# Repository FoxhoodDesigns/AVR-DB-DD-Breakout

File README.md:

# AVR DB/DD Breakout

This little Board is designed to allow for easy experimentation with AVR128DB32 and AVR64DD32 Microcontrollers.
It is very minimalist with only the AVR itself, A pair of standard LDO linear regulators (1117-5V and a 2112-3.3V), A simple power indicator and some jumpers for configuring the board and/or VDDIO2 to 3.3V or 5V.
Note: This relies on the Internal Oscillator which on the new generation of AVR chips can achieve pretty high speeds.

Both the DB and DD work. The DD is more suitable as a general purpose and is fairly cheap (comparable to a ATMega32PB), while the DB is more for bigger stuff. As one might guess by having up to a whopping 128Kb of Flash for code.

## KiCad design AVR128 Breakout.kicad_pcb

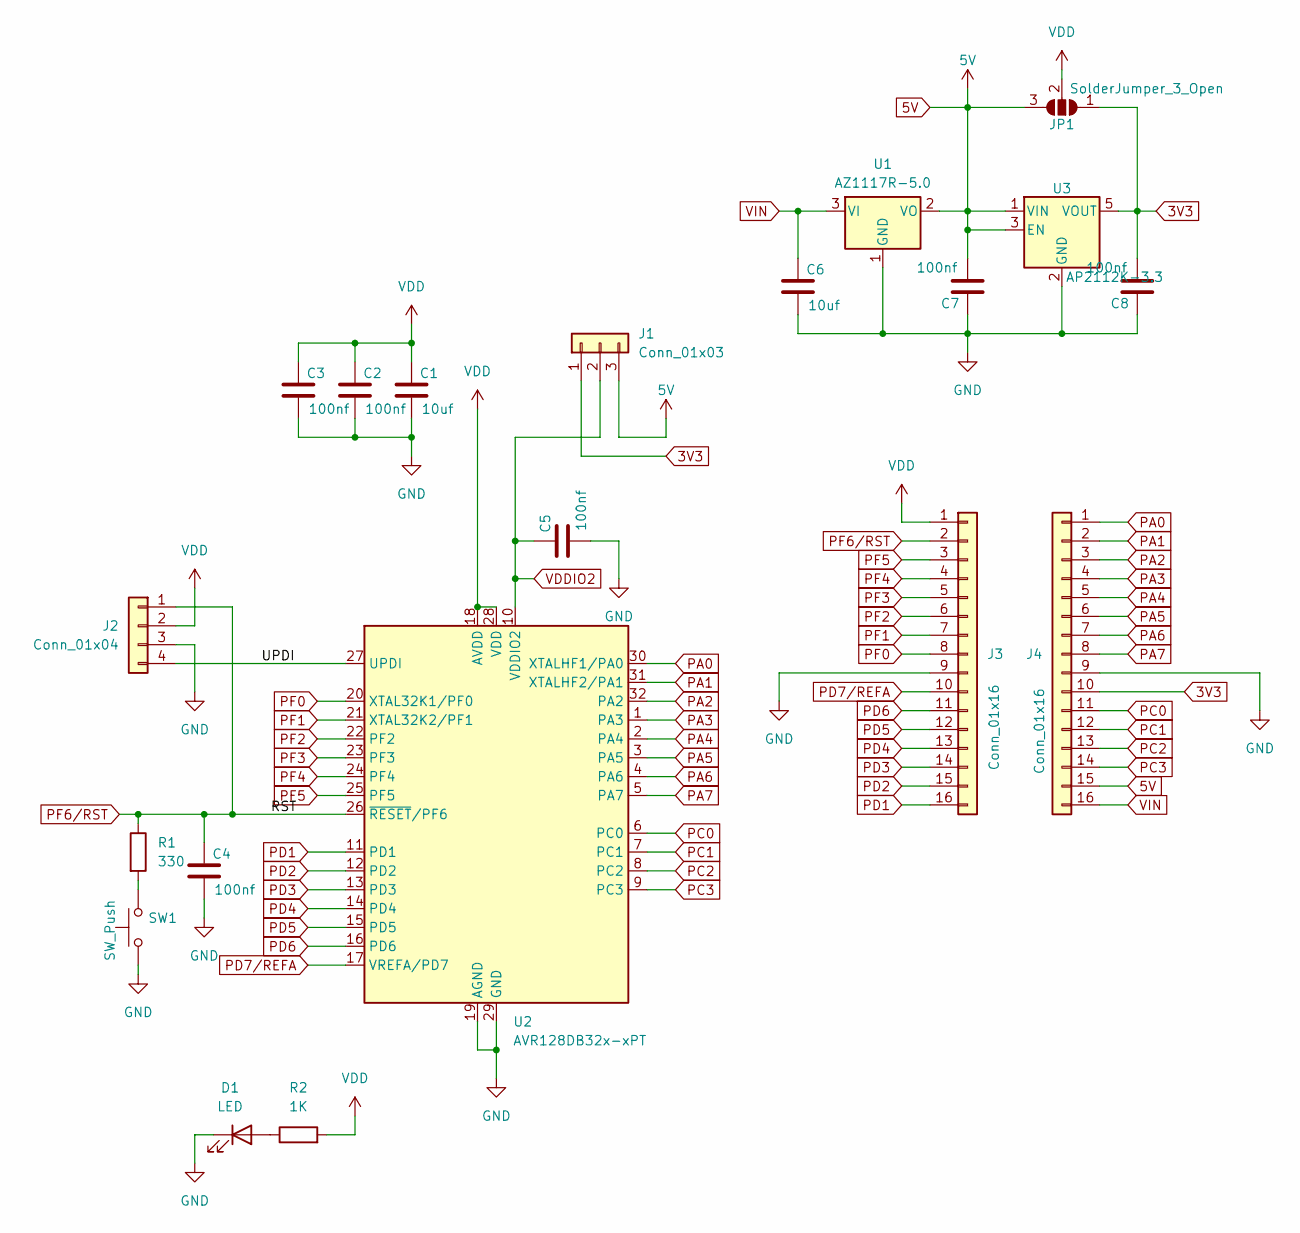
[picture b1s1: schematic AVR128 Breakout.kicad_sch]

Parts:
C1, C6: 10uf; C_1210_3225Metric_Pad1.33x2.70mm_HandSolder
C2, C3, C4, C5, C7, C8: 100nf; C_0805_2012Metric_Pad1.18x1.45mm_HandSolder
D1: LED; LED_0805_2012Metric_Pad1.15x1.40mm_HandSolder
J1: Conn_01x03; PinHeader_1x03_P2.54mm_Vertical
J2: Conn_01x04; PinHeader_1x04_P2.54mm_Vertical
J3, J4: Conn_01x16; PinHeader_1x16_P2.54mm_Vertical
JP1: SolderJumper_3_Open; SolderJumper-3_P1.3mm_Open_Pad1.0x1.5mm_NumberLabels
R1: 330; R_0805_2012Metric_Pad1.20x1.40mm_HandSolder
R2: 1K; R_0805_2012Metric_Pad1.20x1.40mm_HandSolder
SW1: SW_Push; SW_Push_1P1T_NO_Vertical_Wuerth_434133025816
U1: AZ1117R-5.0; SOT-89-3_Handsoldering
U2: AVR128DB32x-xPT; TQFP-32_7x7mm_P0.8mm
U3: AP2112K-3.3; SOT-23-5

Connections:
3V3: C8.2, J1.1, J4.10, JP1.1 (A), U3.5 (VOUT)
5V: C7.2, J1.3, J4.15, JP1.3 (B), U1.2 (VO), U3.1 (VIN), U3.3 (EN)
/UPDI: J2.4, U2.27 (UPDI)
GND: C1.2, C2.2, C3.2, C4.2, C5.2, C6.2, C7.1, C8.1, D1.1 (K), J2.3, J3.9, J4.9, SW1.1, U1.1 (GND), U2.19 (AGND), U2.29 (GND), U3.2 (GND)
unnamed: D1.2 (A), R2.1
unnamed: R1.2, SW1.2
PA0: J4.1, U2.30 (XTALHF1/PA0)
PA1: J4.2, U2.31 (XTALHF2/PA1)
PA2: J4.3, U2.32 (PA2)
PA3: J4.4, U2.1 (PA3)
PA4: J4.5, U2.2 (PA4)
PA5: J4.6, U2.3 (PA5)
PA6: J4.7, U2.4 (PA6)
PA7: J4.8, U2.5 (PA7)
PC0: J4.11, U2.6 (PC0)
PC1: J4.12, U2.7 (PC1)
PC2: J4.13, U2.8 (PC2)
PC3: J4.14, U2.9 (PC3)
PD1: J3.16, U2.11 (PD1)
PD2: J3.15, U2.12 (PD2)
PD3: J3.14, U2.13 (PD3)
PD4: J3.13, U2.14 (PD4)
PD5: J3.12, U2.15 (PD5)
PD6: J3.11, U2.16 (PD6)
PD7/REFA: J3.10, U2.17 (VREFA/PD7)
PF0: J3.8, U2.20 (XTAL32K1/PF0)
PF1: J3.7, U2.21 (XTAL32K2/PF1)
PF2: J3.6, U2.22 (PF2)
PF3: J3.5, U2.23 (PF3)
PF4: J3.4, U2.24 (PF4)
PF5: J3.3, U2.25 (PF5)
PF6/RST: C4.1, J2.1, J3.2, R1.1, U2.26 (~RESET/PF6)
VDD: C1.1, C2.1, C3.1, J2.2, J3.1, JP1.2 (C), R2.2, U2.18 (AVDD), U2.28 (VDD)
VDDIO2: C5.1, J1.2, U2.10 (VDDIO2)
VIN: C6.1, J4.16, U1.3 (VI)

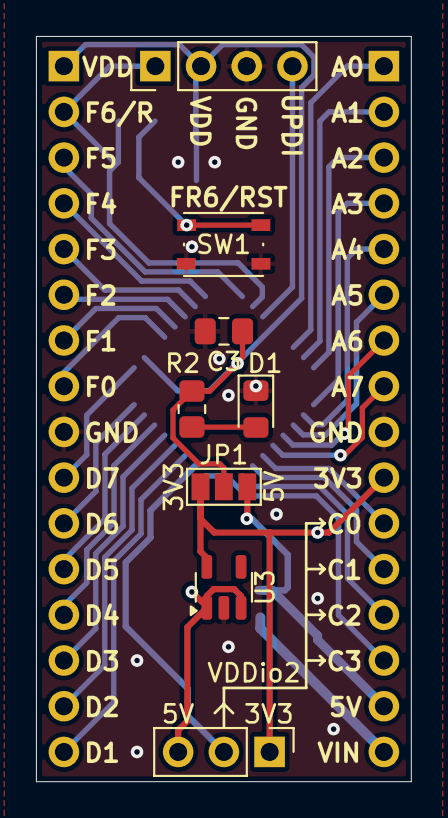
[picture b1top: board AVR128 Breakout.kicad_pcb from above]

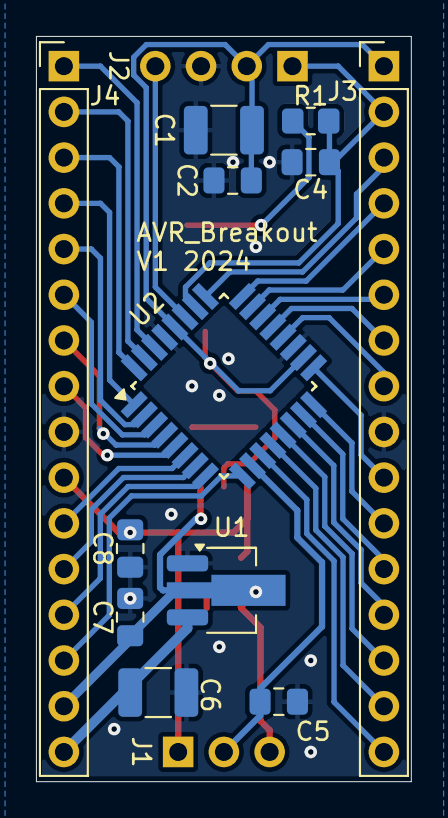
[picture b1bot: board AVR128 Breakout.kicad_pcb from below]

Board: 2 copper layers, 20.8 x 41.4 mm, 20 parts (12 on the bottom side), 35 nets.

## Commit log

2024-08-14 Add files via upload
    Add 3D render of board
2025-02-23 Initial Upload
